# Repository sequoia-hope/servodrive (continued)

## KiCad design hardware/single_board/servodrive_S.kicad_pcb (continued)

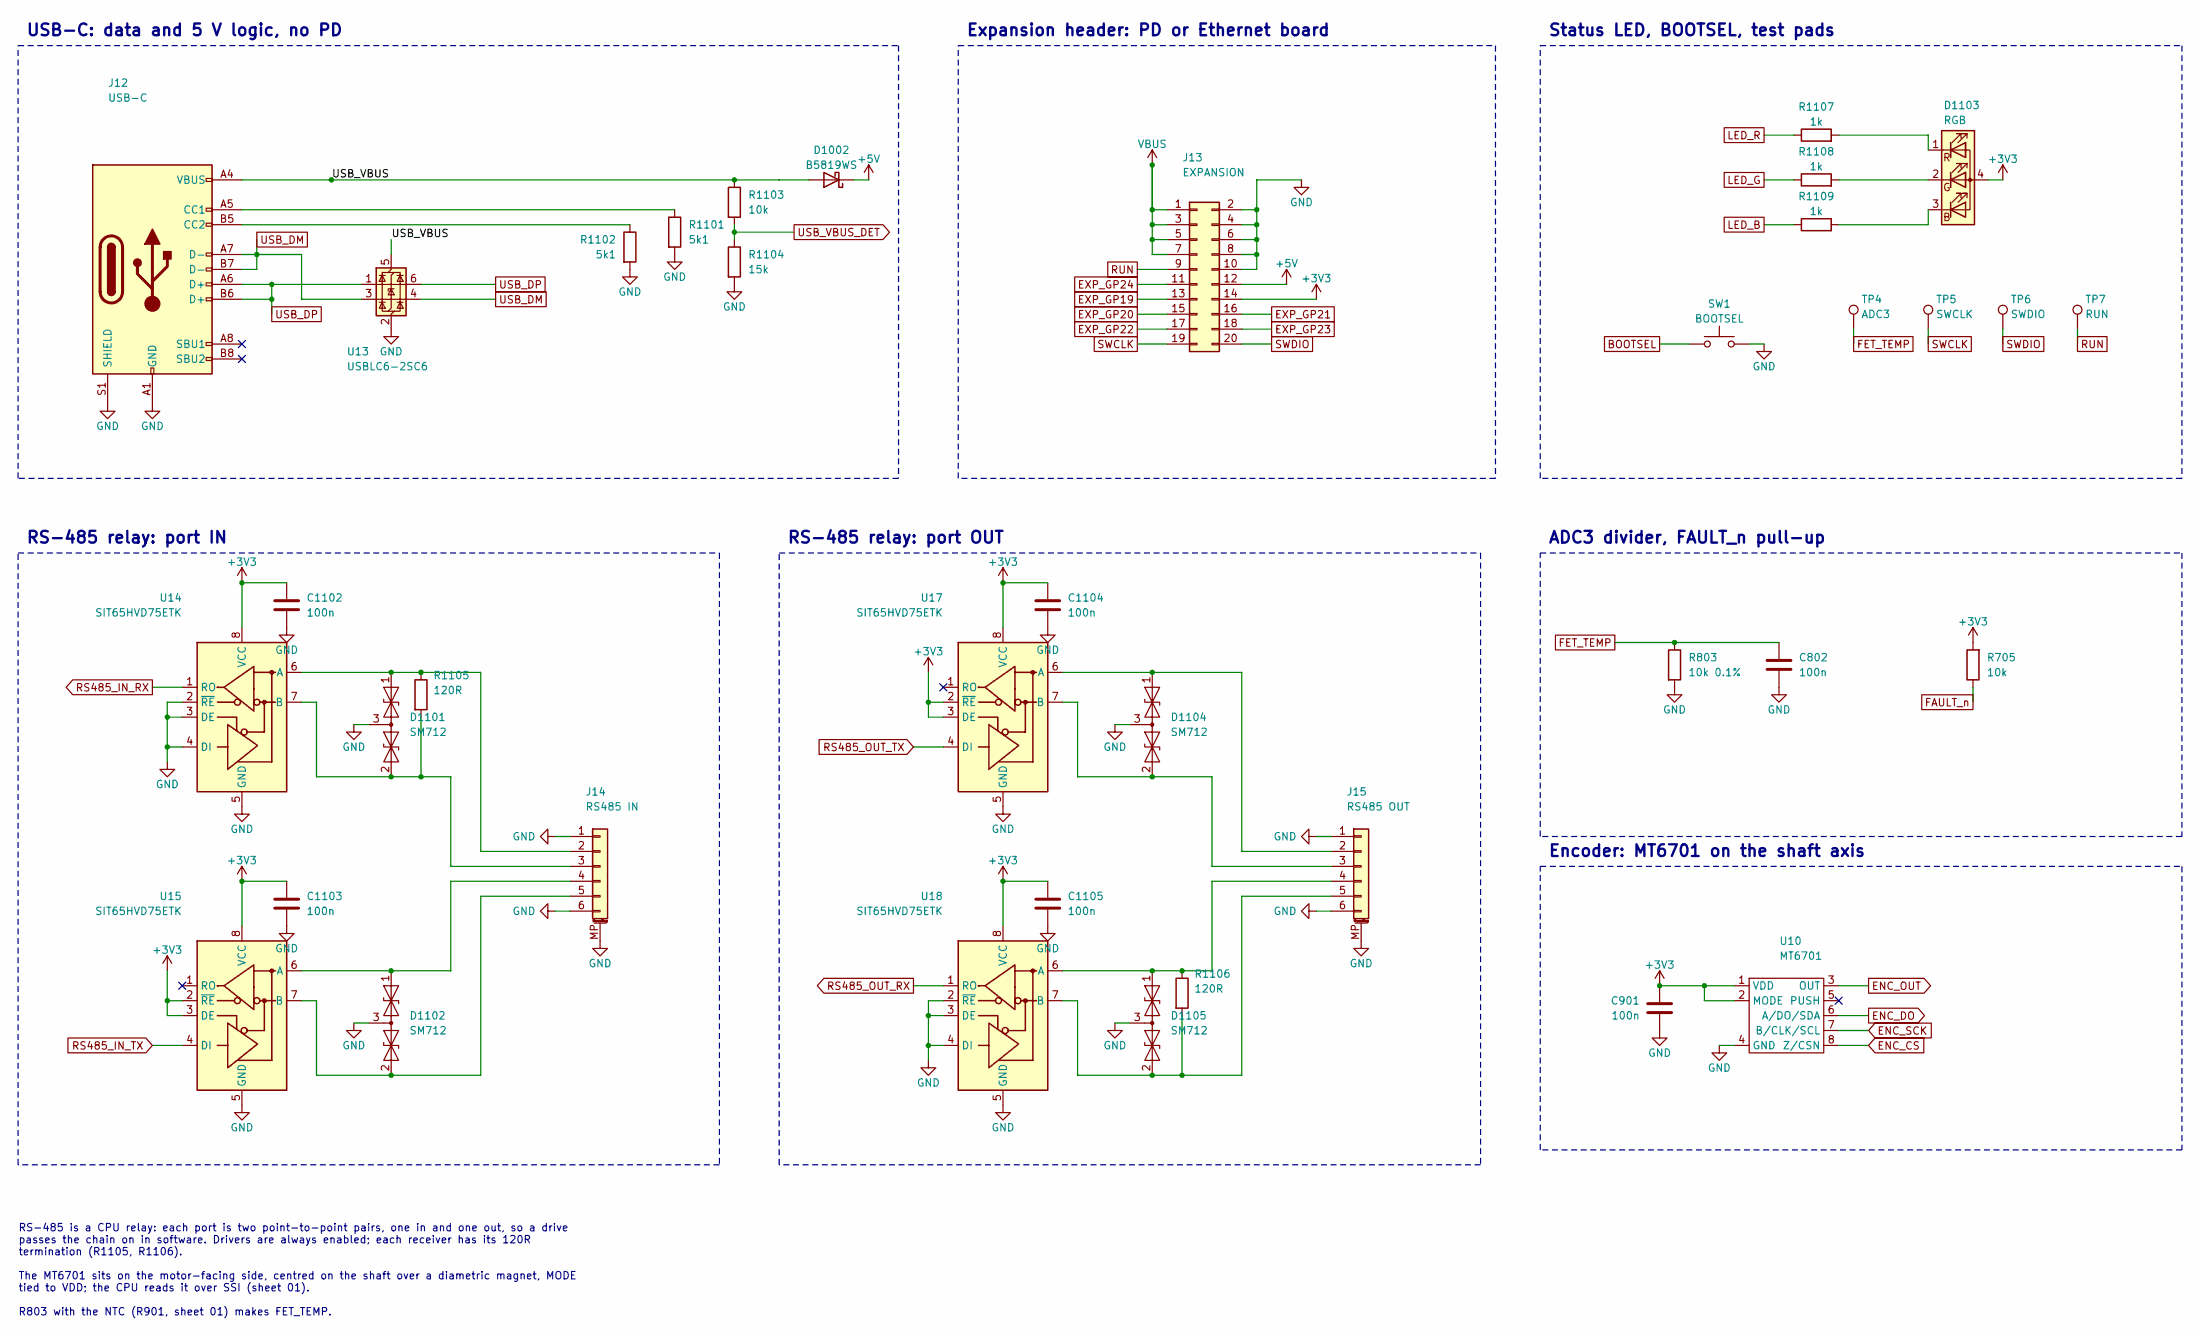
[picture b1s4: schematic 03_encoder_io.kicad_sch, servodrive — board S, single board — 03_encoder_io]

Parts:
C802: 100n; C_0603_1608Metric
C901, C1102, C1103, C1104, C1105: 100n; C_0402_1005Metric
D1002: B5819WS; D_SOD-323
D1101, D1102, D1104, D1105: SM712; SOT-23
D1103: RGB; LED_RGB_1210
J12: USB-C; USB_C_Receptacle_HRO_TYPE-C-31-M-12
J13: EXPANSION; PinHeader_2x10_P1.27mm_Vertical_SMD
J14: RS485 IN; JST_SH_SM06B-SRSS-TB_1x06-1MP_P1.00mm_Horizontal
J15: RS485 OUT; JST_SH_SM06B-SRSS-TB_1x06-1MP_P1.00mm_Horizontal
R705, R1103: 10k; R_0402_1005Metric
R803: 10k 0.1%; R_0603_1608Metric
R1101, R1102: 5k1; R_0402_1005Metric
R1104: 15k; R_0402_1005Metric
R1105, R1106: 120R; R_0603_1608Metric
R1107, R1108, R1109: 1k; R_0402_1005Metric
SW1: BOOTSEL; SW_SPST_B3U-1000P
TP4: ADC3; TestPoint_Pad_D1.0mm
TP5: SWCLK; TestPoint_Pad_D1.0mm
TP6: SWDIO; TestPoint_Pad_D1.0mm
TP7: RUN; TestPoint_Pad_D1.0mm
U10: MT6701; SOIC-8_3.9x4.9mm_P1.27mm
U13: USBLC6-2SC6; SOT-23-6
U14, U15, U17, U18: SIT65HVD75ETK; DFN-8_L3.0-W3.0-P0.65-BL-EP

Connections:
+3V3: C901.1, C1102.1, C1103.1, C1104.1, C1105.1, D1103.4 (A), J13.14, R705.2, U10.1 (VDD), U10.2 (MODE), U14.8 (VCC), U15.2 (~RE), U15.3 (DE), U15.8 (VCC), U17.2 (~RE), U17.3 (DE), U17.8 (VCC), U18.8 (VCC); also elsewhere on the board
+5V: D1002.1 (K), J13.12; also elsewhere on the board
BOOTSEL: SW1.1; also elsewhere on the board
CC1: J12.A5 (CC1), R1101.1
CC2: J12.B5 (CC2), R1102.1
ENC_CS: U10.8 (Z/CSN); also elsewhere on the board
ENC_DO: U10.6 (A/DO/SDA); also elsewhere on the board
ENC_OUT: U10.3 (OUT); also elsewhere on the board
ENC_SCK: U10.7 (B/CLK/SCL); also elsewhere on the board
EXP_GP19: J13.13; also elsewhere on the board
EXP_GP20: J13.15; also elsewhere on the board
EXP_GP21: J13.16; also elsewhere on the board
EXP_GP22: J13.17; also elsewhere on the board
EXP_GP23: J13.18; also elsewhere on the board
EXP_GP24: J13.11; also elsewhere on the board
FAULT_n: R705.1; also elsewhere on the board
FET_TEMP: C802.1, R803.1, TP4.1; also elsewhere on the board
GND: C802.2, C901.2, C1102.2, C1103.2, C1104.2, C1105.2, D1101.3 (common), D1102.3 (common), D1104.3 (common), D1105.3 (common), J12.A1 (GND), J12.A12 (GND), J12.B1 (GND), J12.B12 (GND), J12.S1 (SHIELD), J13.2, J13.4, J13.6, J13.8, J13.10, J14.1, J14.6, J14.MP (MountPin), J15.1, J15.6, J15.MP (MountPin), R803.2, R1101.2, R1102.2, R1104.2, SW1.2, U10.4 (GND), U13.2 (GND), U14.2 (~RE), U14.3 (DE), U14.4 (DI), U14.5 (GND), U15.5 (GND), U17.5 (GND), U18.2 (~RE), U18.3 (DE), U18.4 (DI), U18.5 (GND); also elsewhere on the board
LED_B: R1109.1; also elsewhere on the board
LED_B_K: D1103.3 (BK), R1109.2
LED_G: R1108.1; also elsewhere on the board
LED_G_K: D1103.2 (GK), R1108.2
LED_R: R1107.1; also elsewhere on the board
LED_R_K: D1103.1 (RK), R1107.2
RS485_IN_DN_N: D1101.2 (A2), J14.3, R1105.2, U14.7 (B)
RS485_IN_DN_P: D1101.1 (A1), J14.2, R1105.1, U14.6 (A)
RS485_IN_RX: U14.1 (RO); also elsewhere on the board
RS485_IN_TX: U15.4 (DI); also elsewhere on the board
RS485_IN_UP_N: D1102.2 (A2), J14.5, U15.7 (B)
RS485_IN_UP_P: D1102.1 (A1), J14.4, U15.6 (A)
RS485_OUT_DN_N: D1104.2 (A2), J15.3, U17.7 (B)
RS485_OUT_DN_P: D1104.1 (A1), J15.2, U17.6 (A)
RS485_OUT_RX: U18.1 (RO); also elsewhere on the board
RS485_OUT_TX: U17.4 (DI); also elsewhere on the board
RS485_OUT_UP_N: D1105.2 (A2), J15.5, R1106.2, U18.7 (B)
RS485_OUT_UP_P: D1105.1 (A1), J15.4, R1106.1, U18.6 (A)
RUN: J13.9, TP7.1; also elsewhere on the board
SWCLK: J13.19, TP5.1; also elsewhere on the board
SWDIO: J13.20, TP6.1; also elsewhere on the board
USB_DM: J12.A7 (D-), J12.B7 (D-), U13.3 (I/O2), U13.4 (I/O2); also elsewhere on the board
USB_DP: J12.A6 (D+), J12.B6 (D+), U13.1 (I/O1), U13.6 (I/O1); also elsewhere on the board
USB_VBUS: D1002.2 (A), J12.A4 (VBUS), J12.A9 (VBUS), J12.B4 (VBUS), J12.B9 (VBUS), R1103.1, U13.5 (VBUS)
USB_VBUS_DET: R1103.2, R1104.1; also elsewhere on the board
VBUS: J13.1, J13.3, J13.5, J13.7; also elsewhere on the board

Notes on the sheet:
USB-C: data and 5 V logic, no PD
RS-485 relay: port IN
RS-485 relay: port OUT
Expansion header: PD or Ethernet board
Status LED, BOOTSEL, test pads
ADC3 divider, FAULT_n pull-up
Encoder: MT6701 on the shaft axis
RS-485 is a CPU relay: each port is two point-to-point pairs, one in and one out, so a drive passes the chain on in software. Drivers are always enabled; each receiver has its 120R termination (R1105, R1106). The MT6701 sits on the motor-facing side, centred on the shaft over a diametric magnet, MO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

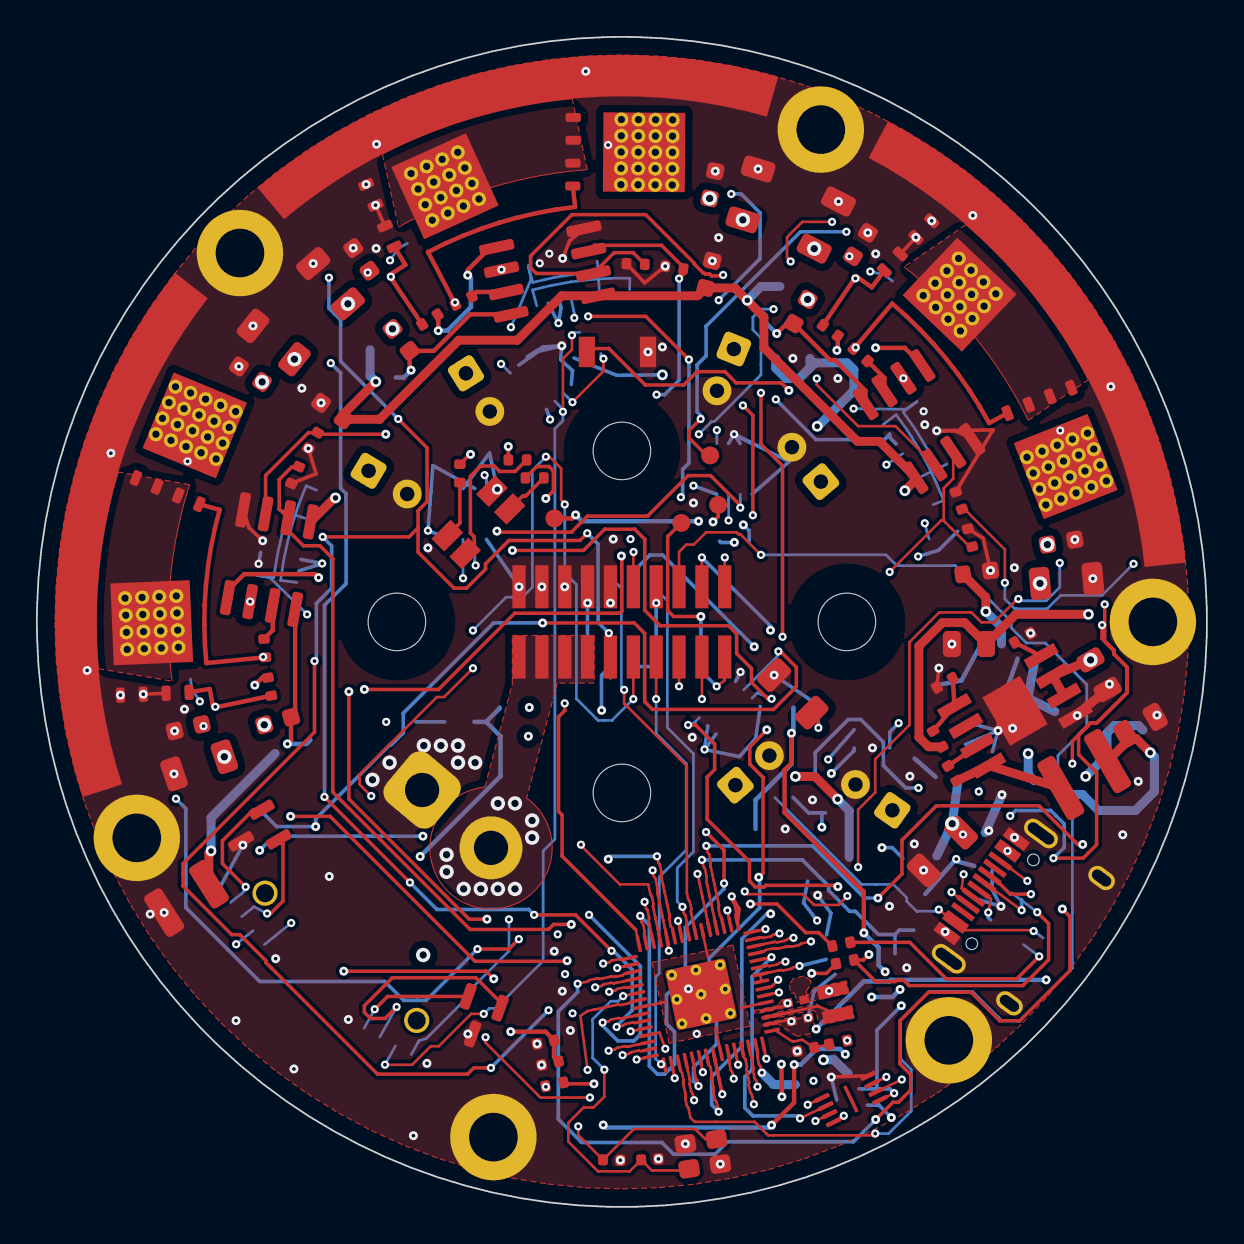
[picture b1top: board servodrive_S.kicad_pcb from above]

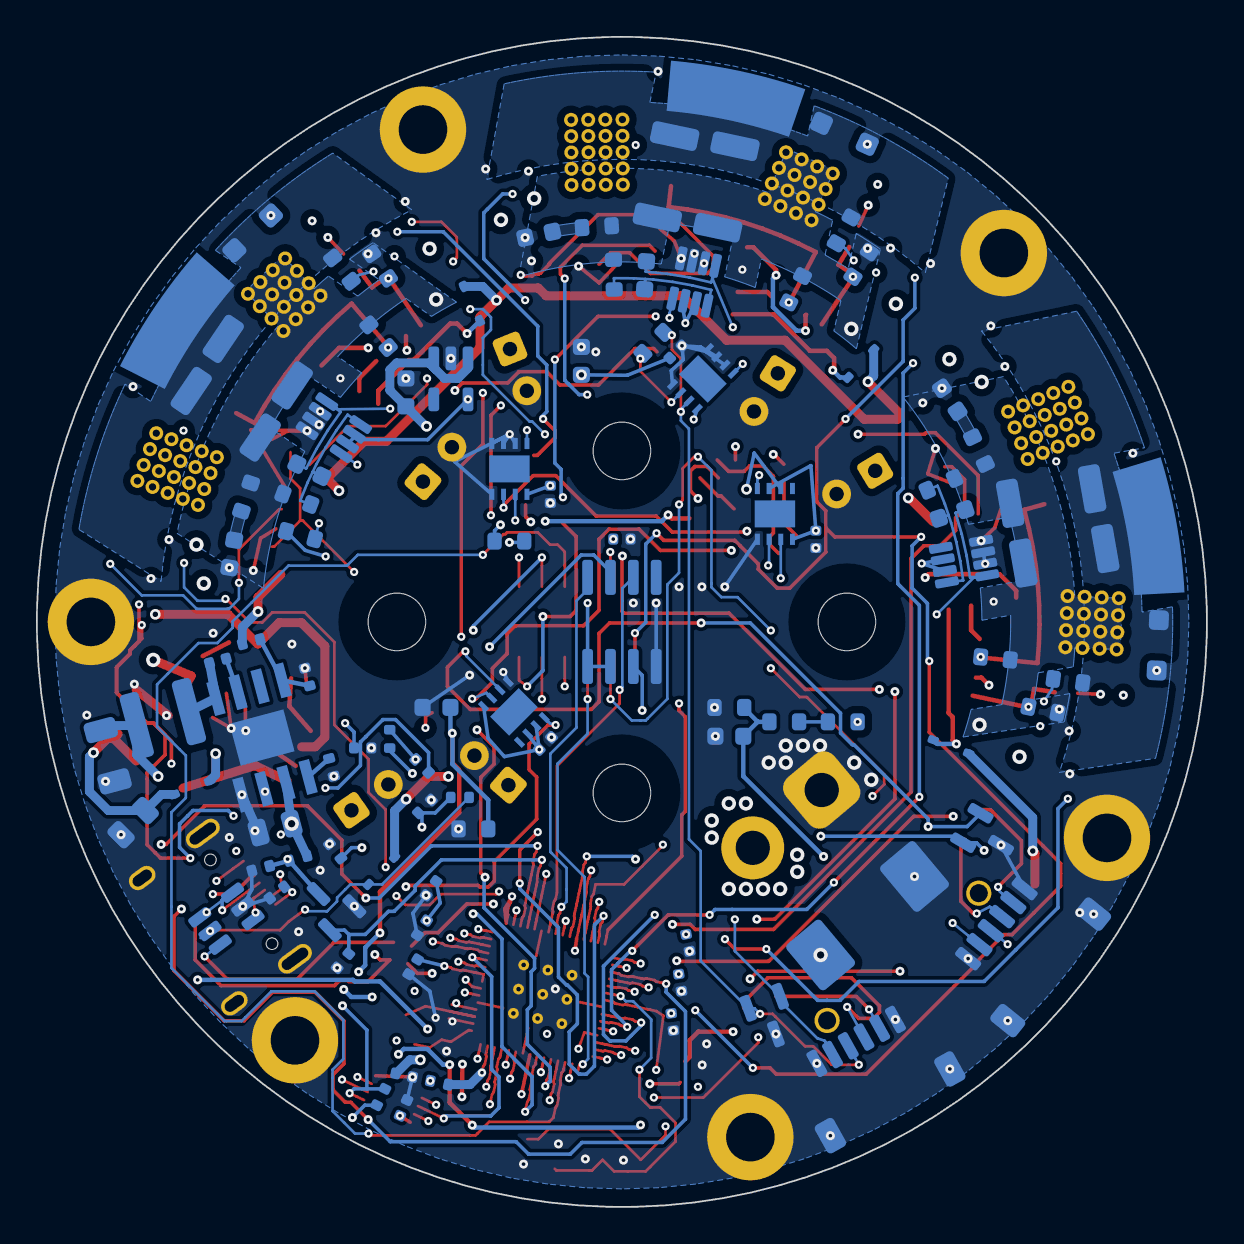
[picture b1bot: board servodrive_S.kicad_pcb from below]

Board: 6 copper layers, 65.0 x 65.0 mm, 198 parts (99 on the bottom side), 111 nets.

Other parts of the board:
H1, H2, H3, H4: MountingHole_3.2mm_M3

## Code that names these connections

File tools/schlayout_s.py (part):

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    "ADC_AVDD is +3V3 filtered by R703 and C716 (+3V3A).",
    "BOOTSEL: SW1 on sheet 03 pulls QSPI_SS low through R701 at reset.",
    encoder_note(comps),
    "GPIO19-24 go to the expansion header (sheet 03).",
    width=62)


def encoder_note(comps):
    do, sck, cs, out = (gpio(comps, n) for n in ("ENC_DO", "ENC_SCK", "ENC_CS", "ENC_OUT"))
    spi = do == 4 and sck == 6
    return (f"The encoder: ENC_DO on GPIO{do}, ENC_SCK on GPIO{sck}, ENC_CS on GPIO{cs}, "
            f"ENC_OUT on GPIO{out}" + (" -- SPI0's RX and SCK, so SPI0 reads it." if spi
                                      else ". SPI0 would want the data on GPIO4 and the "
                                           "clock on GPIO6."))


def control_body(s):
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
    # reset: RC on RUN, which also leaves for the header and a test pad
    s.wire(u["26"], (61, 58), (61, 60), (37, 60))
    s.label(s.g(37, 60), "RUN", stub=0, d=(-1, 0))
    s.place("R704", 43, 58.5, rot=180, fields="right")
    s.place("C717", 40, 61.5, fields="left")
    for n in ("24", "25"):
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    s.wire((89, 29), s["R707"]["2"])
    s.wire((90, 32), s["R708"]["2"])
    s.wire(s["R707"]["1"], (98, 29))
    s.label(s.g(98, 29), "USB_DP", stub=0, d=(1, 0))
    s.wire(s["R708"]["1"], (98, 32))
    s.label(s.g(98, 32), "USB_DM", stub=0, d=(1, 0))
    for p in u.pins.values():
        if p.d == (1, 0) and p.net and p.num not in ("52", "51"):
            s.label(p, stub=2)
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    for n in ("6", "5", "2", "3", "7"):
        s.label(f[n], stub=2)
    s.wire(f["1"], (13, 41))
    s.label(s.g(13, 41), "QSPI_SS", stub=0, d=(-1, 0))
    s.place("R701", 14, 39.5, rot=180, fields="right")
    s.label(s["R701"]["2"], stub=1, d=(0, -1), text_dir=(-1, 0))
    s.wire(f["8"], (19, 37), (23, 37))
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        fet = s.place(q, *P(-18, 1), fields=(-2.5, 3.2, "right"))
        s.place(r_g, *P(-24, 2.5), fields="left")
        s.wire(fet["1"], P(-28, 1))
        s.label(s.g(*P(-28, 1)), "GATE_OFF", stub=0, d=(-1, 0), shape="input")
    # RT to ground
    s.wire(u["4"], P(-6, 1), P(-6, 2))
    s.place(rrt, *P(-6, 3.5), fields="left")
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
def power_supply_notes():
    """The sheet's notes, from the netlist's own choices: which cans are the
    bulk, and which GPIO GATE_OFF is on (it moved from 14 to 2)."""
    refs = S.bulk_refs()
    bulk = (" and ".join(refs) if len(refs) == 2 else
            ", ".join(refs[:-1]) + " and " + refs[-1])
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        f"it; {bulk} are the bulk. VBUS_SENSE = VBUS x 4k7 / 116k7 "
        "(0.1 %), on ADC2.",
        "12 V gate rail: LMR38010, starting at 9.9 V on the R1003/R1004 divider. "
        f"GATE_OFF (GPIO{gate_off}) high turns Q1001 on and stops the rail, taking the "
        "gate drivers' supply away. R1005 holds it low through reset, so the rail "
        "comes up and the drivers brake the motor.",
        "5 V logic rail: LMR38010, diode-ORed with USB (D1002, sheet 03) through "
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    s.place("C801", 51 + dx, 21.5, fields="right")
    s.wire((45 + dx, 19), (51 + dx, 19), (51 + dx, 20))
    s.wire((51 + dx, 19), (56 + dx, 19))
    s.label(s.g(56 + dx, 19), "VBUS_SENSE", stub=0, d=(1, 0), shape="output")

    s.block("12 V gate rail", 3, 31, 73, 53)
    x, y = buck(s, 36, 43, "U11", ("C1003", "C1004"), "C1005", "L1001", ("C603", "C1009"),
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    e = s.place("U13", 26, 21, fields=(-3, 5, "left"))
    s.wire((18, 21), e["1"])
    s.wire((17, 19), (20, 19), (20, 22), e["3"])
    s.label(s.g(18, 22), "USB_DP", stub=1, d=(0, 1), text_dir=(1, 0))
    s.label(s.g(17, 19), "USB_DM", stub=1, d=(0, -1), text_dir=(1, 0))
    s.wire(e["6"], (33, 21))
    s.label(s.g(33, 21), "USB_DP", stub=0, d=(1, 0))
    s.wire(e["4"], (33, 22))
    s.label(s.g(33, 22), "USB_DM", stub=0, d=(1, 0))
    s.label(e["5"], "USB_VBUS", stub=1, text_dir=(1, 0))
    s.wire(j["A4"], (52, 14))
    s.label(s.g(22, 14), "USB_VBUS", stub=0, d=(1, 0))
    s.wire(j["A5"], (45, 16))
    s.wire(j["B5"], (42, 17))
    s.place("R1101", 45, 17.5, fields="right")
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    s.place("R1104", 49, 19.5, fields="right")
    s.wire(s["R1103"]["2"], s["R1104"]["1"])
    s.wire((49, 17.5), (53, 17.5))
    s.label(s.g(53, 17.5), "USB_VBUS_DET", stub=0, d=(1, 0), shape="output")
    s.place("D1002", 55.5, 14, rot=180, fields="above")
    s.wire((52, 14), s["D1002"]["2"])
    s.power(s["D1002"]["1"], "+5V", stub=1)
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    s.place("C802", 119, 46.5, fields="right")
    s.wire((112, 45), (119, 45))
    s.wire((112, 45), (108, 45))
    s.label(s.g(108, 45), "FET_TEMP", stub=0, d=(-1, 0))
    s.place("R705", 132, 46.5, rot=180, fields="right")
    s.label(s["R705"]["1"], stub=1, d=(0, 1), text_dir=(-1, 0))

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
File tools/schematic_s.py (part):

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    its 54 V bus TVS
  - the GPIO map: 0/1 are UART0 for RS-485 port IN and 14/15 a PIO UART
    for port OUT (the CPU relays between them); 2 is GATE_OFF and 3 FAULT_n;
    the encoder's SCK and DO swap to GPIO6 and 4 so SPI0 can read it; 19-24
    go to the expansion header; USB_VBUS_DET moves to 25
  - J7, J8, J9 and TP1-TP3 go; C603 and C604 become the two bucks' output
    caps; TP4 moves to the centre with three new test pads beside it
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        # what high does. A reset leaves the pin pulled down, the rail on and
        # the low sides braking, which is what spec sec.3 asks of a reset.
        #
        # GATE_OFF and FAULT_n on GPIO2/3, port OUT's PIO UART on 14/15
        # (asked 2026-09-26). On 14/15 the first two left the RP2350 on the
        # side facing away from Q1001 and R705, and with keepouts round the
        # motor screws that side's corridor was one track short: the router
        # always left one of GATE_OFF, FAULT_n, RUN, LED_R open. GPIO0-3 are
        # the pads nearest Q1001; port OUT's transceivers sit on 14/15's side.
        # A PIO UART takes any pins, and GPIO2 is pulled down through reset
        # just as 14 was.
        2: "GATE_OFF", 3: "FAULT_n", 14: "RS485_OUT_TX", 15: "RS485_OUT_RX",
        # The encoder on hardware SPI0 (asked 2026-09-24). GPIO4-7 are SPI0's
        # RX, CSn, SCK and TX, and board A's map had the clock on 4 and the
        # data on 6 -- SPI0's RX and SCK, the wrong way round for a
        # peripheral that only talks. Swapped: DO into RX, SCK out of SCK.
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# ground beside each of those pins, so a PD board feeding the bus through
# here passes the encoder as a dipole, not a loop.
#
# RUN and GPIO24 are on the odd row, which faces the CPU, and +5V and +3V3 on
# the even row (2026-09-24): with a keepout round the motor screw at (0, -9.5)
# on both faces, everything the CPU sends to the header crosses on In3 alone,
# and two more signals on the far row were more than that corridor holds.
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                "A7": "USB_DM", "B7": "USB_DM", "A8": "", "B8": ""})
    add("J12", "Connector:USB_C_Receptacle_USB2.0_16P", "USB-C",
        "Connector_USB:USB_C_Receptacle_HRO_TYPE-C-31-M-12", usb, gu)
    # Pin 5 on USB_VBUS is safe here: the port is a 5 V sink with no PD
    # (spec F-39 is about a 20 V contract on this pin).
    add("U13", "Power_Protection:USBLC6-2SC6", "USBLC6-2SC6", "Package_TO_SOT_SMD:SOT-23-6",
        {"1": "USB_DP", "6": "USB_DP", "3": "USB_DM", "4": "USB_DM",
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    add("R1102", R, "5k1", FP_R["0402"], {"1": "CC2", "2": "GND"}, gu)
    add("D1002", SCHOTTKY, "B5819WS", "Diode_SMD:D_SOD-323",
        {"1": "+5V", "2": "USB_VBUS"}, gu)
    # 5 V -> 3.0 V on GPIO25
    add("R1103", R, "10k", FP_R["0402"], {"1": "USB_VBUS", "2": "USB_VBUS_DET"}, gu)
    add("R1104", R, "15k", FP_R["0402"], {"1": "USB_VBUS_DET", "2": "GND"}, gu)

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
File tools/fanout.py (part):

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    return (c.x, c.y), (ux, uy), (-uy, ux), half

# F.Cu tracks of the reference design (RP-006440), chip frame, mm, KiCad
# y-down: pin 50 (DVDD) to the regulator's output pour, pin 46 (VREG_AVDD)
# to its capacitor and the 33R. Read off the reference board.
REF_TRACKS = {
    "50": [(1.2, -3.44), (1.18, -4.12), (0.93, -4.38), (0.93, -5.12)],
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    ring = {z.GetNetCode() for z in board.Zones() if z.GetZoneName().startswith("1V1 ring")}
    # ... judged by the zone's OUTLINE, not its fill: between two neighbouring
    # pads the fill of a pour is 0.3 mm wide and breaks at their corners, so
    # the fill under VREG_LX's pad is an island. The stub these pins get
    # reaches past that into the body of the pour.
    covered = set()
    for p in pads:
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    # Two F.Cu tracks copied from the reference design (RP-006440), in the
    # chip's own frame: DVDD pin 50 out past the VIN capacitor into the
    # regulator's output pour -- which is how the 1V1 ring under the chip
    # meets the 1V1 the regulator makes -- and VREG_AVDD pin 46 out to its
    # 4u7 and the 33R. Each begins at its pin's centre.
    ref_tracks = 0
    for num, pts in REF_TRACKS.items():
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                            and legal(local, code, layer, segs, w=0.2):
                        # Meeting a neighbour's tap at the via at a sliver's
                        # angle -- the MT6701's VDD pins did, 20 degrees,
                        # once board S's J13 put EXP_GP24 over the pin that
                        # carried the via: straight to that pad instead.
                        o = sliver_pad(board, code, vp, pts[-2])
                        if o is not None:
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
